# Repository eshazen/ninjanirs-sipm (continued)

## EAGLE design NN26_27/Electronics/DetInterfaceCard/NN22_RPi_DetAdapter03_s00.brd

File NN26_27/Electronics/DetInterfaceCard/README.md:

## Detector card V03

Two variants:

| Designator | NN24-26        | NN27  | Notes                             |
|------------|----------------|-------|-----------------------------------|
| R71        | DNP            | 0 Ohm | New component / designator        |
| LF1        | BLM18AG601SN1D | DNP   | Ferrite 600 Ohm @ 100 MHz, 500 mA |

Additional components could be DNP’d in NN27 if desired, such as U13 and C104.

**2026-08-24**

Trying to order.  Two problem parts:

C89 etc.  10uF X5R 0402

D1-D2  SBR1A20T5-7  1A fast response diode.  A problem.

Possible sub:  SBR1U40LP-7 in DFN package about the same size.
Make this change in `develop` (KiCAD conversion).  Layout done.

BOM is a problem... the KiCAD import doesnt include MPN.

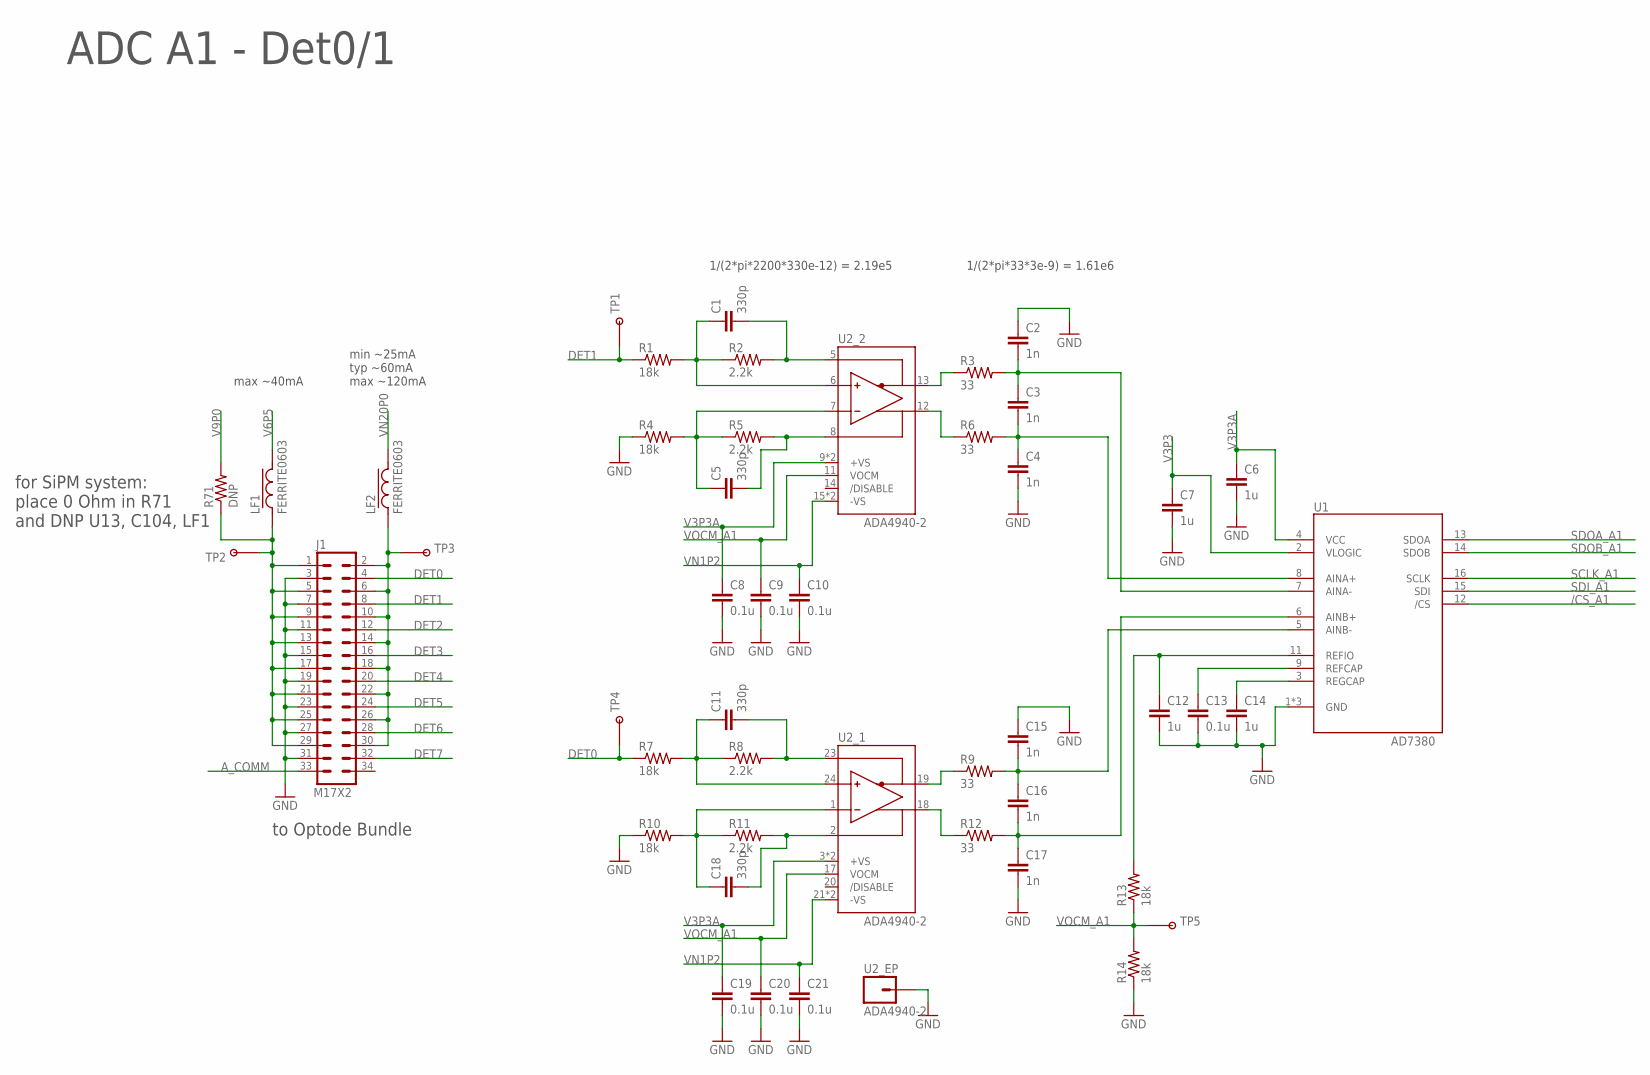
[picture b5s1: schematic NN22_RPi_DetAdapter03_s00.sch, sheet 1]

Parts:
C1, C5, C11, C18: 330p; 0402-CAP
C2, C3, C4, C15, C16, C17: 1n; 0402-CAP
C6, C7, C12, C14: 1u; 0402-CAP
C8, C9, C10, C13, C19, C20, C21: 0.1u; 0402-CAP
J1: M17X2; M17X2_0.050_SHF
LF1, LF2: FERRITE0603; 0603-FER
R1, R4, R7, R10, R13, R14: 18k; 0402-RES
R2, R5, R8, R11: 2.2k; 0402-RES
R3, R6, R9, R12: 33; 0402-RES
R71: DNP; 0402-RES
TP1, TP2, TP3, TP4, TP5: TESTPOINT_ROUND; TESTPAD_ROUND
U1: AD7380; LFCSP16
U2: ADA4940-2; LFCSP24

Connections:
/CS_A1: U1.12 (/CS); also elsewhere on the board
A_COMM: J1.33; also elsewhere on the board
DET0: J1.4, R7.1, TP4.P$1
DET1: J1.8, R1.1, TP1.P$1
DET2: J1.12; also elsewhere on the board
DET3: J1.16; also elsewhere on the board
DET4: J1.20; also elsewhere on the board
DET5: J1.24; also elsewhere on the board
DET6: J1.28; also elsewhere on the board
DET7: J1.32; also elsewhere on the board
GND: C2.1, C4.2, C6.2, C7.2, C8.2, C9.2, C10.2, C12.2, C13.2, C14.2, C15.1, C17.2, C19.2, C20.2, C21.2, J1.3, J1.7, J1.11, J1.15, J1.19, J1.23, J1.27, J1.31, R4.1, R10.1, R14.1, U1.1 (GND), U1.10 (GND), U1.EP (GND), U2.EP (1); also elsewhere on the board
unnamed: R3.1, U2.13 (-OUT)
unnamed: R6.1, U2.12 (+OUT)
unnamed: C2.2, C3.1, R3.2, U1.7 (AINA-)
unnamed: C3.2, C4.1, R6.2, U1.8 (AINA+)
unnamed: C11.2, R8.2, U2.23 (-FB)
unnamed: C12.1, R13.2, U1.11 (REFIO)
unnamed: C13.1, U1.9 (REFCAP)
unnamed: C14.1, U1.3 (REGCAP)
unnamed: C18.2, R11.2, U2.2 (+FB)
unnamed: R9.1, U2.19 (-OUT)
unnamed: R12.1, U2.18 (+OUT)
unnamed: C15.2, C16.1, R9.2, U1.5 (AINB-)
unnamed: C16.2, C17.1, R12.2, U1.6 (AINB+)
unnamed: C1.1, R1.2, R2.1, U2.6 (+IN)
unnamed: C1.2, R2.2, U2.5 (-FB)
unnamed: C5.2, R5.2, U2.8 (+FB)
unnamed: C5.1, R4.2, R5.1, U2.7 (-IN)
unnamed: C11.1, R7.2, R8.1, U2.24 (+IN)
unnamed: C18.1, R10.2, R11.1, U2.1 (-IN)
SCLK_A1: U1.16 (SCLK); also elsewhere on the board
SDI_A1: U1.15 (SDI); also elsewhere on the board
SDOA_A1: U1.13 (SDOA); also elsewhere on the board
SDOB_A1: U1.14 (SDOB); also elsewhere on the board
V3P3: C7.1, U1.2 (VLOGIC); also elsewhere on the board
V3P3A: C6.1, C8.1, C19.1, U1.4 (VCC), U2.3 (+VS), U2.4 (+VS), U2.9 (+VS), U2.10 (+VS); also elsewhere on the board
V6P5: LF1.2; also elsewhere on the board
V6P5CON: J1.1, J1.5, J1.9, J1.13, J1.17, J1.21, J1.25, J1.29, LF1.1, R71.1, TP2.P$1
V9P0: R71.2; also elsewhere on the board
VN1P2: C10.1, C21.1, U2.15 (-VS), U2.16 (-VS), U2.21 (-VS), U2.22 (-VS); also elsewhere on the board
VN20P0: LF2.2; also elsewhere on the board
VN20P0CON: J1.2, J1.6, J1.10, J1.14, J1.18, J1.22, J1.26, J1.30, LF2.1, TP3.P$1
VOCM_A1: C9.1, C20.1, R13.1, R14.2, TP5.P$1, U2.11 (VOCM), U2.17 (VOCM)

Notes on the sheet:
max ~40mA
min ~25mA typ ~60mA max ~120mA
to Optode Bundle
ADC A1 - Det0/1
1/(2*pi*33*3e-9) = 1.61e6
1/(2*pi*2200*330e-12) = 2.19e5
for SiPM system: place 0 Ohm in R71 and DNP U13, C104, LF1

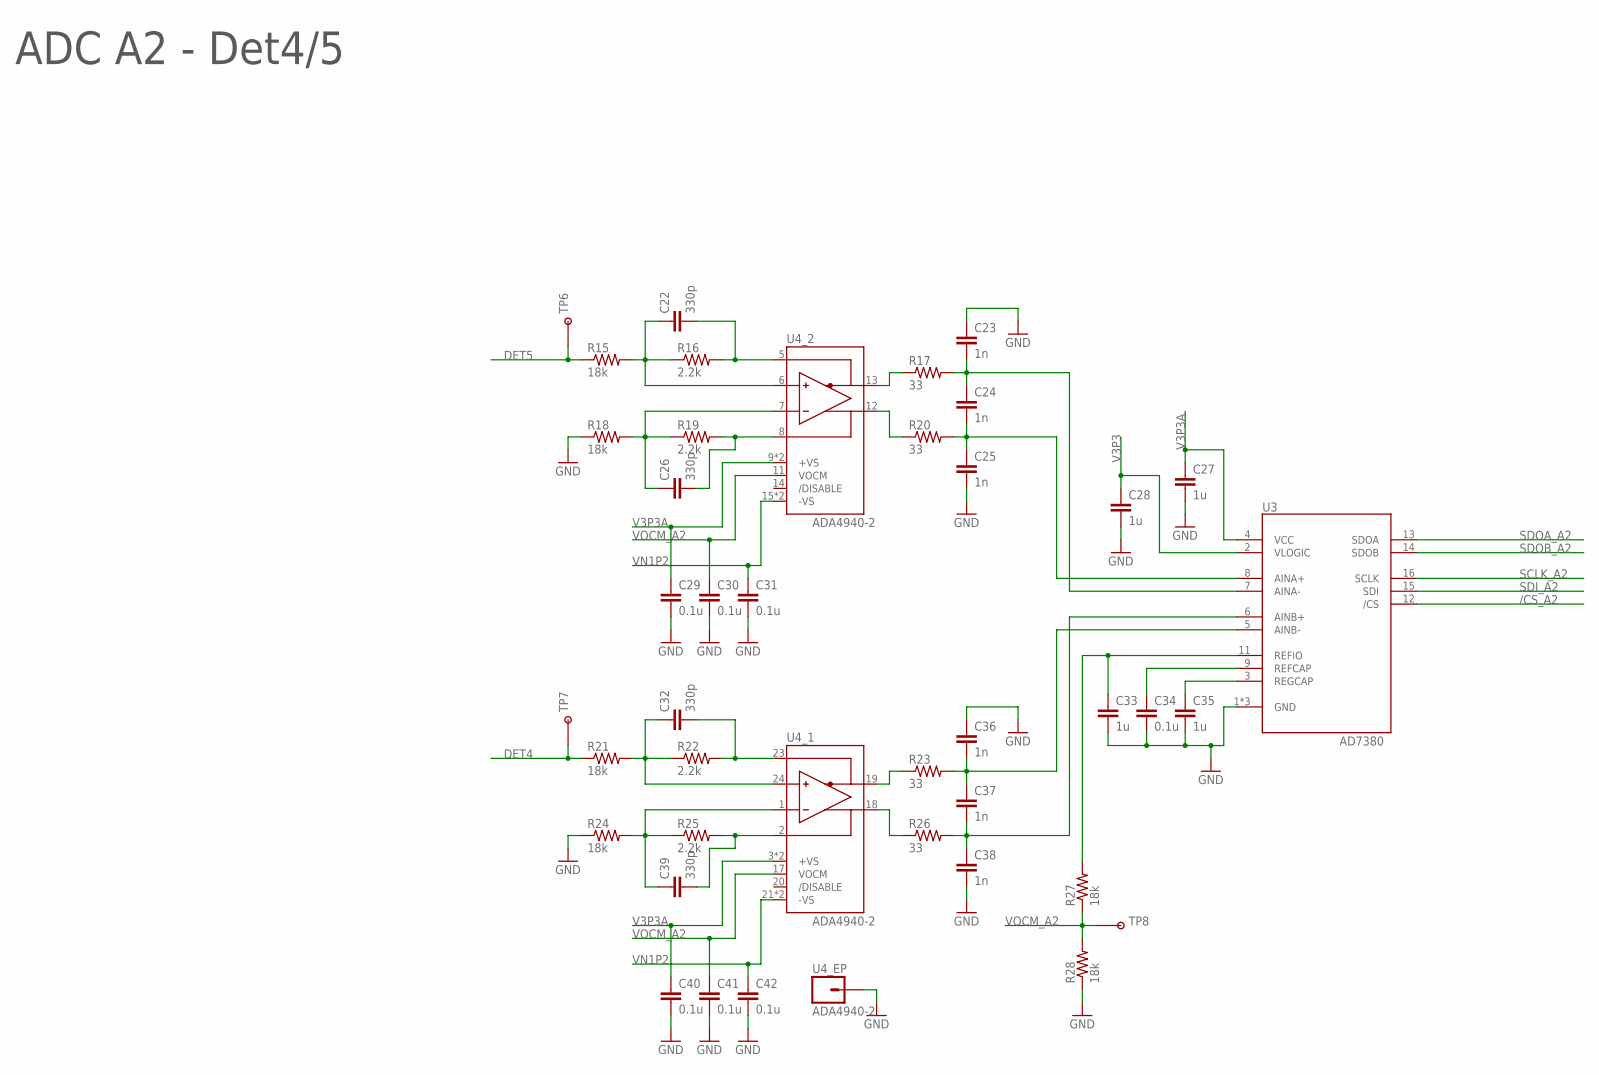
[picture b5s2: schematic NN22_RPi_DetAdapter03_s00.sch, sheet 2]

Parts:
C22, C26, C32, C39: 330p; 0402-CAP
C23, C24, C25, C36, C37, C38: 1n; 0402-CAP
C27, C28, C33, C35: 1u; 0402-CAP
C29, C30, C31, C34, C40, C41, C42: 0.1u; 0402-CAP
R15, R18, R21, R24, R27, R28: 18k; 0402-RES
R16, R19, R22, R25: 2.2k; 0402-RES
R17, R20, R23, R26: 33; 0402-RES
TP6, TP7, TP8: TESTPOINT_ROUND; TESTPAD_ROUND
U3: AD7380; LFCSP16
U4: ADA4940-2; LFCSP24

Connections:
/CS_A2: U3.12 (/CS); also elsewhere on the board
DET4: R21.1, TP7.P$1; also elsewhere on the board
DET5: R15.1, TP6.P$1; also elsewhere on the board
GND: C23.1, C25.2, C27.2, C28.2, C29.2, C30.2, C31.2, C33.2, C34.2, C35.2, C36.1, C38.2, C40.2, C41.2, C42.2, R18.1, R24.1, R28.1, U3.1 (GND), U3.10 (GND), U3.EP (GND), U4.EP (1); also elsewhere on the board
unnamed: R17.1, U4.13 (-OUT)
unnamed: R20.1, U4.12 (+OUT)
unnamed: C23.2, C24.1, R17.2, U3.7 (AINA-)
unnamed: C24.2, C25.1, R20.2, U3.8 (AINA+)
unnamed: C33.1, R27.2, U3.11 (REFIO)
unnamed: C34.1, U3.9 (REFCAP)
unnamed: C35.1, U3.3 (REGCAP)
unnamed: R23.1, U4.19 (-OUT)
unnamed: R26.1, U4.18 (+OUT)
unnamed: C36.2, C37.1, R23.2, U3.5 (AINB-)
unnamed: C37.2, C38.1, R26.2, U3.6 (AINB+)
unnamed: C22.1, R15.2, R16.1, U4.6 (+IN)
unnamed: C22.2, R16.2, U4.5 (-FB)
unnamed: C26.2, R19.2, U4.8 (+FB)
unnamed: C26.1, R18.2, R19.1, U4.7 (-IN)
unnamed: C32.1, R21.2, R22.1, U4.24 (+IN)
unnamed: C39.1, R24.2, R25.1, U4.1 (-IN)
unnamed: C32.2, R22.2, U4.23 (-FB)
unnamed: C39.2, R25.2, U4.2 (+FB)
SCLK_A2: U3.16 (SCLK); also elsewhere on the board
SDI_A2: U3.15 (SDI); also elsewhere on the board
SDOA_A2: U3.13 (SDOA); also elsewhere on the board
SDOB_A2: U3.14 (SDOB); also elsewhere on the board
V3P3: C28.1, U3.2 (VLOGIC); also elsewhere on the board
V3P3A: C27.1, C29.1, C40.1, U3.4 (VCC), U4.3 (+VS), U4.4 (+VS), U4.9 (+VS), U4.10 (+VS); also elsewhere on the board
VN1P2: C31.1, C42.1, U4.15 (-VS), U4.16 (-VS), U4.21 (-VS), U4.22 (-VS); also elsewhere on the board
VOCM_A2: C30.1, C41.1, R27.1, R28.2, TP8.P$1, U4.11 (VOCM), U4.17 (VOCM)

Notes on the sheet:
ADC A2 - Det4/5

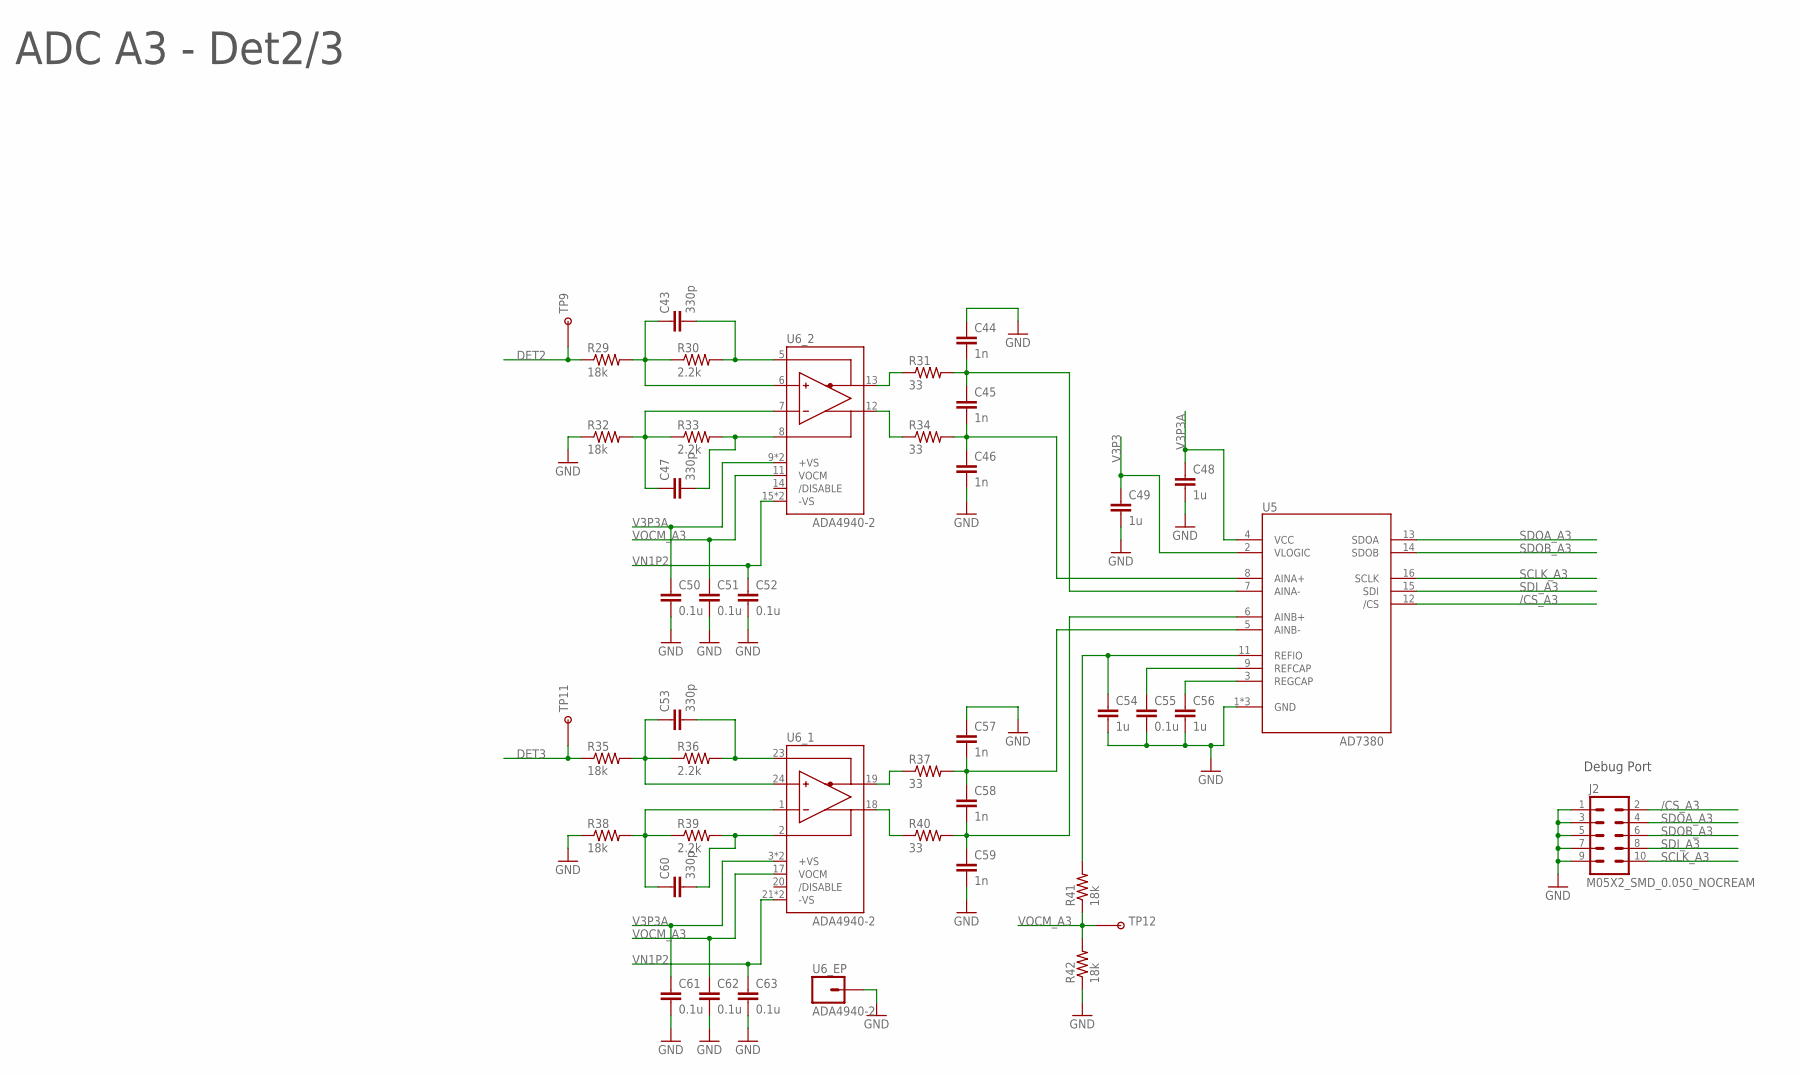
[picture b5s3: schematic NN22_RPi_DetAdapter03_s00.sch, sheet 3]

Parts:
C43, C47, C53, C60: 330p; 0402-CAP
C44, C45, C46, C57, C58, C59: 1n; 0402-CAP
C48, C49, C54, C56: 1u; 0402-CAP
C50, C51, C52, C55, C61, C62, C63: 0.1u; 0402-CAP
J2: M05X2_SMD_0.050_NOCREAM; M05X2_0.050_SMD_NO_CREAM
R29, R32, R35, R38, R41, R42: 18k; 0402-RES
R30, R33, R36, R39: 2.2k; 0402-RES
R31, R34, R37, R40: 33; 0402-RES
TP9, TP11, TP12: TESTPOINT_ROUND; TESTPAD_ROUND
U5: AD7380; LFCSP16
U6: ADA4940-2; LFCSP24

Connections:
/CS_A3: J2.2, U5.12 (/CS); also elsewhere on the board
DET2: R29.1, TP9.P$1; also elsewhere on the board
DET3: R35.1, TP11.P$1; also elsewhere on the board
GND: C44.1, C46.2, C48.2, C49.2, C50.2, C51.2, C52.2, C54.2, C55.2, C56.2, C57.1, C59.2, C61.2, C62.2, C63.2, J2.1, J2.3, J2.5, J2.7, J2.9, R32.1, R38.1, R42.1, U5.1 (GND), U5.10 (GND), U5.EP (GND), U6.EP (1); also elsewhere on the board
unnamed: R31.1, U6.13 (-OUT)
unnamed: R34.1, U6.12 (+OUT)
unnamed: C44.2, C45.1, R31.2, U5.7 (AINA-)
unnamed: C45.2, C46.1, R34.2, U5.8 (AINA+)
unnamed: C54.1, R41.2, U5.11 (REFIO)
unnamed: C55.1, U5.9 (REFCAP)
unnamed: C56.1, U5.3 (REGCAP)
unnamed: R37.1, U6.19 (-OUT)
unnamed: R40.1, U6.18 (+OUT)
unnamed: C57.2, C58.1, R37.2, U5.5 (AINB-)
unnamed: C58.2, C59.1, R40.2, U5.6 (AINB+)
unnamed: C43.1, R29.2, R30.1, U6.6 (+IN)
unnamed: C43.2, R30.2, U6.5 (-FB)
unnamed: C47.2, R33.2, U6.8 (+FB)
unnamed: C47.1, R32.2, R33.1, U6.7 (-IN)
unnamed: C53.1, R35.2, R36.1, U6.24 (+IN)
unnamed: C60.1, R38.2, R39.1, U6.1 (-IN)
unnamed: C53.2, R36.2, U6.23 (-FB)
unnamed: C60.2, R39.2, U6.2 (+FB)
SCLK_A3: J2.10, U5.16 (SCLK); also elsewhere on the board
SDI_A3: J2.8, U5.15 (SDI); also elsewhere on the board
SDOA_A3: J2.4, U5.13 (SDOA); also elsewhere on the board
SDOB_A3: J2.6, U5.14 (SDOB); also elsewhere on the board
V3P3: C49.1, U5.2 (VLOGIC); also elsewhere on the board
V3P3A: C48.1, C50.1, C61.1, U5.4 (VCC), U6.3 (+VS), U6.4 (+VS), U6.9 (+VS), U6.10 (+VS); also elsewhere on the board
VN1P2: C52.1, C63.1, U6.15 (-VS), U6.16 (-VS), U6.21 (-VS), U6.22 (-VS); also elsewhere on the board
VOCM_A3: C51.1, C62.1, R41.1, R42.2, TP12.P$1, U6.11 (VOCM), U6.17 (VOCM)

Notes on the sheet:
Debug Port
ADC A3 - Det2/3

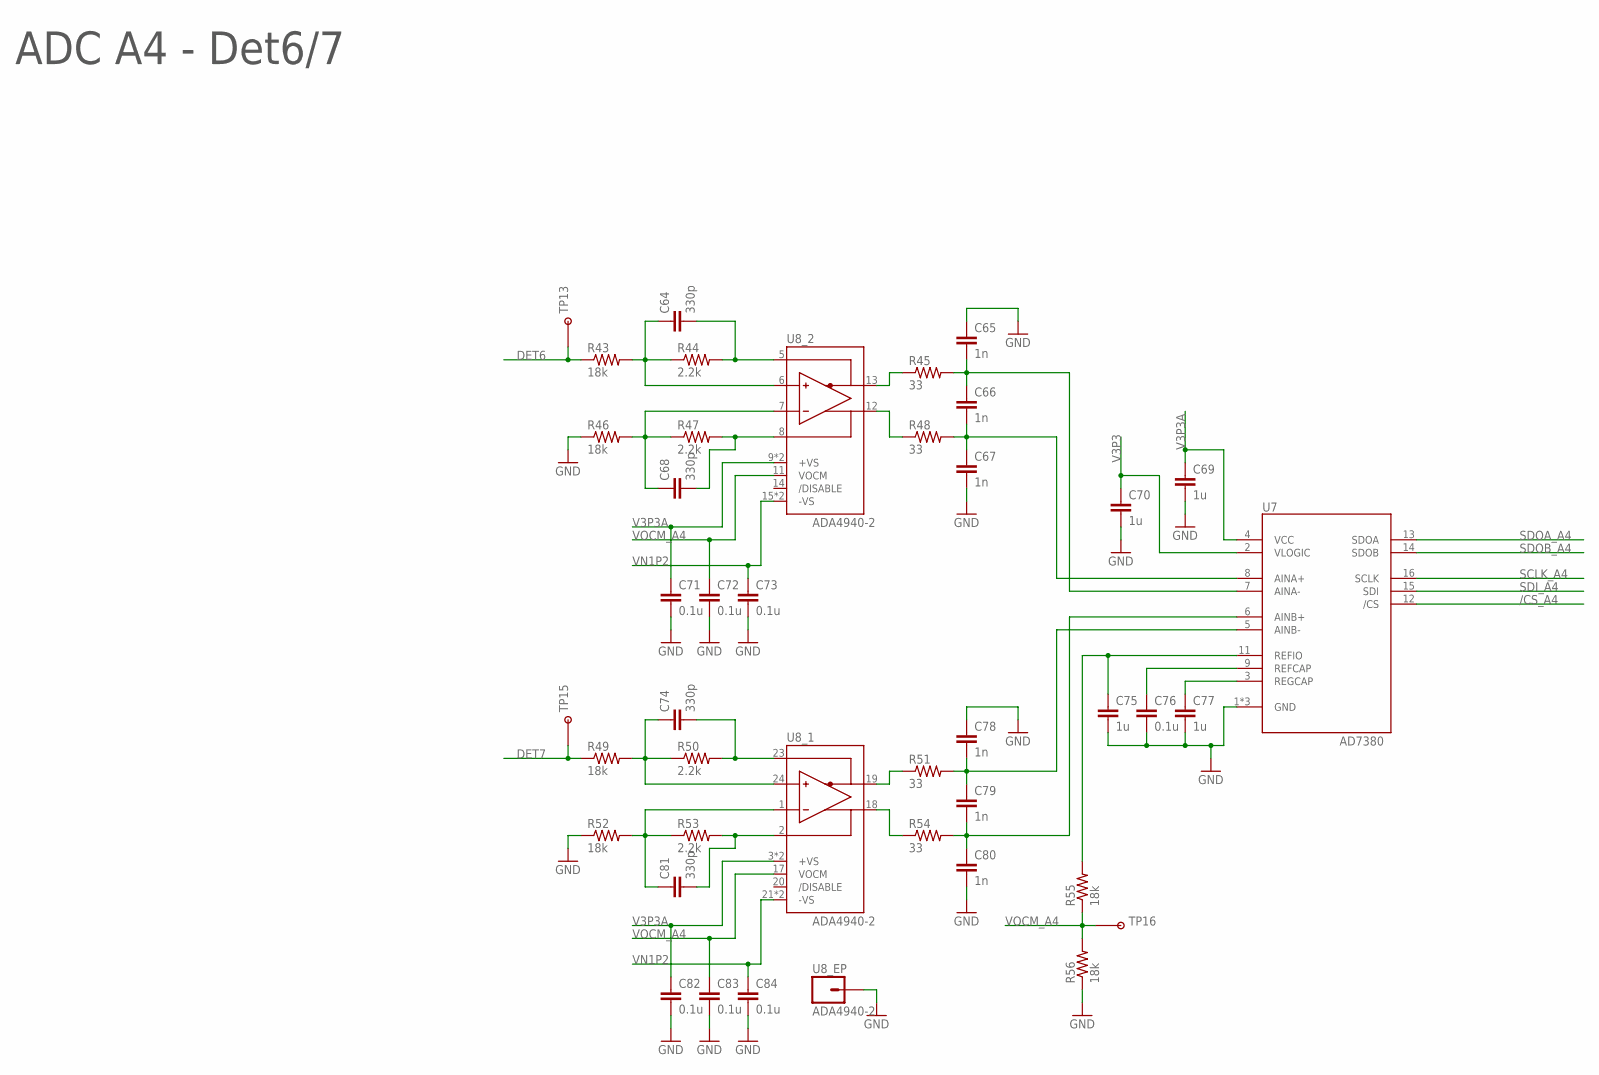
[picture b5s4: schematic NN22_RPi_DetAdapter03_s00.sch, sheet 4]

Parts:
C64, C68, C74, C81: 330p; 0402-CAP
C65, C66, C67, C78, C79, C80: 1n; 0402-CAP
C69, C70, C75, C77: 1u; 0402-CAP
C71, C72, C73, C76, C82, C83, C84: 0.1u; 0402-CAP
R43, R46, R49, R52, R55, R56: 18k; 0402-RES
R44, R47, R50, R53: 2.2k; 0402-RES
R45, R48, R51, R54: 33; 0402-RES
TP13, TP15, TP16: TESTPOINT_ROUND; TESTPAD_ROUND
U7: AD7380; LFCSP16
U8: ADA4940-2; LFCSP24

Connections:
/CS_A4: U7.12 (/CS); also elsewhere on the board
DET6: R43.1, TP13.P$1; also elsewhere on the board
DET7: R49.1, TP15.P$1; also elsewhere on the board
GND: C65.1, C67.2, C69.2, C70.2, C71.2, C72.2, C73.2, C75.2, C76.2, C77.2, C78.1, C80.2, C82.2, C83.2, C84.2, R46.1, R52.1, R56.1, U7.1 (GND), U7.10 (GND), U7.EP (GND), U8.EP (1); also elsewhere on the board
unnamed: R45.1, U8.13 (-OUT)
unnamed: R48.1, U8.12 (+OUT)
unnamed: C65.2, C66.1, R45.2, U7.7 (AINA-)
unnamed: C66.2, C67.1, R48.2, U7.8 (AINA+)
unnamed: C75.1, R55.2, U7.11 (REFIO)
unnamed: C76.1, U7.9 (REFCAP)
unnamed: C77.1, U7.3 (REGCAP)
unnamed: R51.1, U8.19 (-OUT)
unnamed: R54.1, U8.18 (+OUT)
unnamed: C78.2, C79.1, R51.2, U7.5 (AINB-)
unnamed: C79.2, C80.1, R54.2, U7.6 (AINB+)
unnamed: C64.1, R43.2, R44.1, U8.6 (+IN)
unnamed: C64.2, R44.2, U8.5 (-FB)
unnamed: C68.2, R47.2, U8.8 (+FB)
unnamed: C68.1, R46.2, R47.1, U8.7 (-IN)
unnamed: C74.1, R49.2, R50.1, U8.24 (+IN)
unnamed: C81.1, R52.2, R53.1, U8.1 (-IN)
unnamed: C74.2, R50.2, U8.23 (-FB)
unnamed: C81.2, R53.2, U8.2 (+FB)
SCLK_A4: U7.16 (SCLK); also elsewhere on the board
SDI_A4: U7.15 (SDI); also elsewhere on the board
SDOA_A4: U7.13 (SDOA); also elsewhere on the board
SDOB_A4: U7.14 (SDOB); also elsewhere on the board
V3P3: C70.1, U7.2 (VLOGIC); also elsewhere on the board
V3P3A: C69.1, C71.1, C82.1, U7.4 (VCC), U8.3 (+VS), U8.4 (+VS), U8.9 (+VS), U8.10 (+VS); also elsewhere on the board
VN1P2: C73.1, C84.1, U8.15 (-VS), U8.16 (-VS), U8.21 (-VS), U8.22 (-VS); also elsewhere on the board
VOCM_A4: C72.1, C83.1, R55.1, R56.2, TP16.P$1, U8.11 (VOCM), U8.17 (VOCM)

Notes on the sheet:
ADC A4 - Det6/7

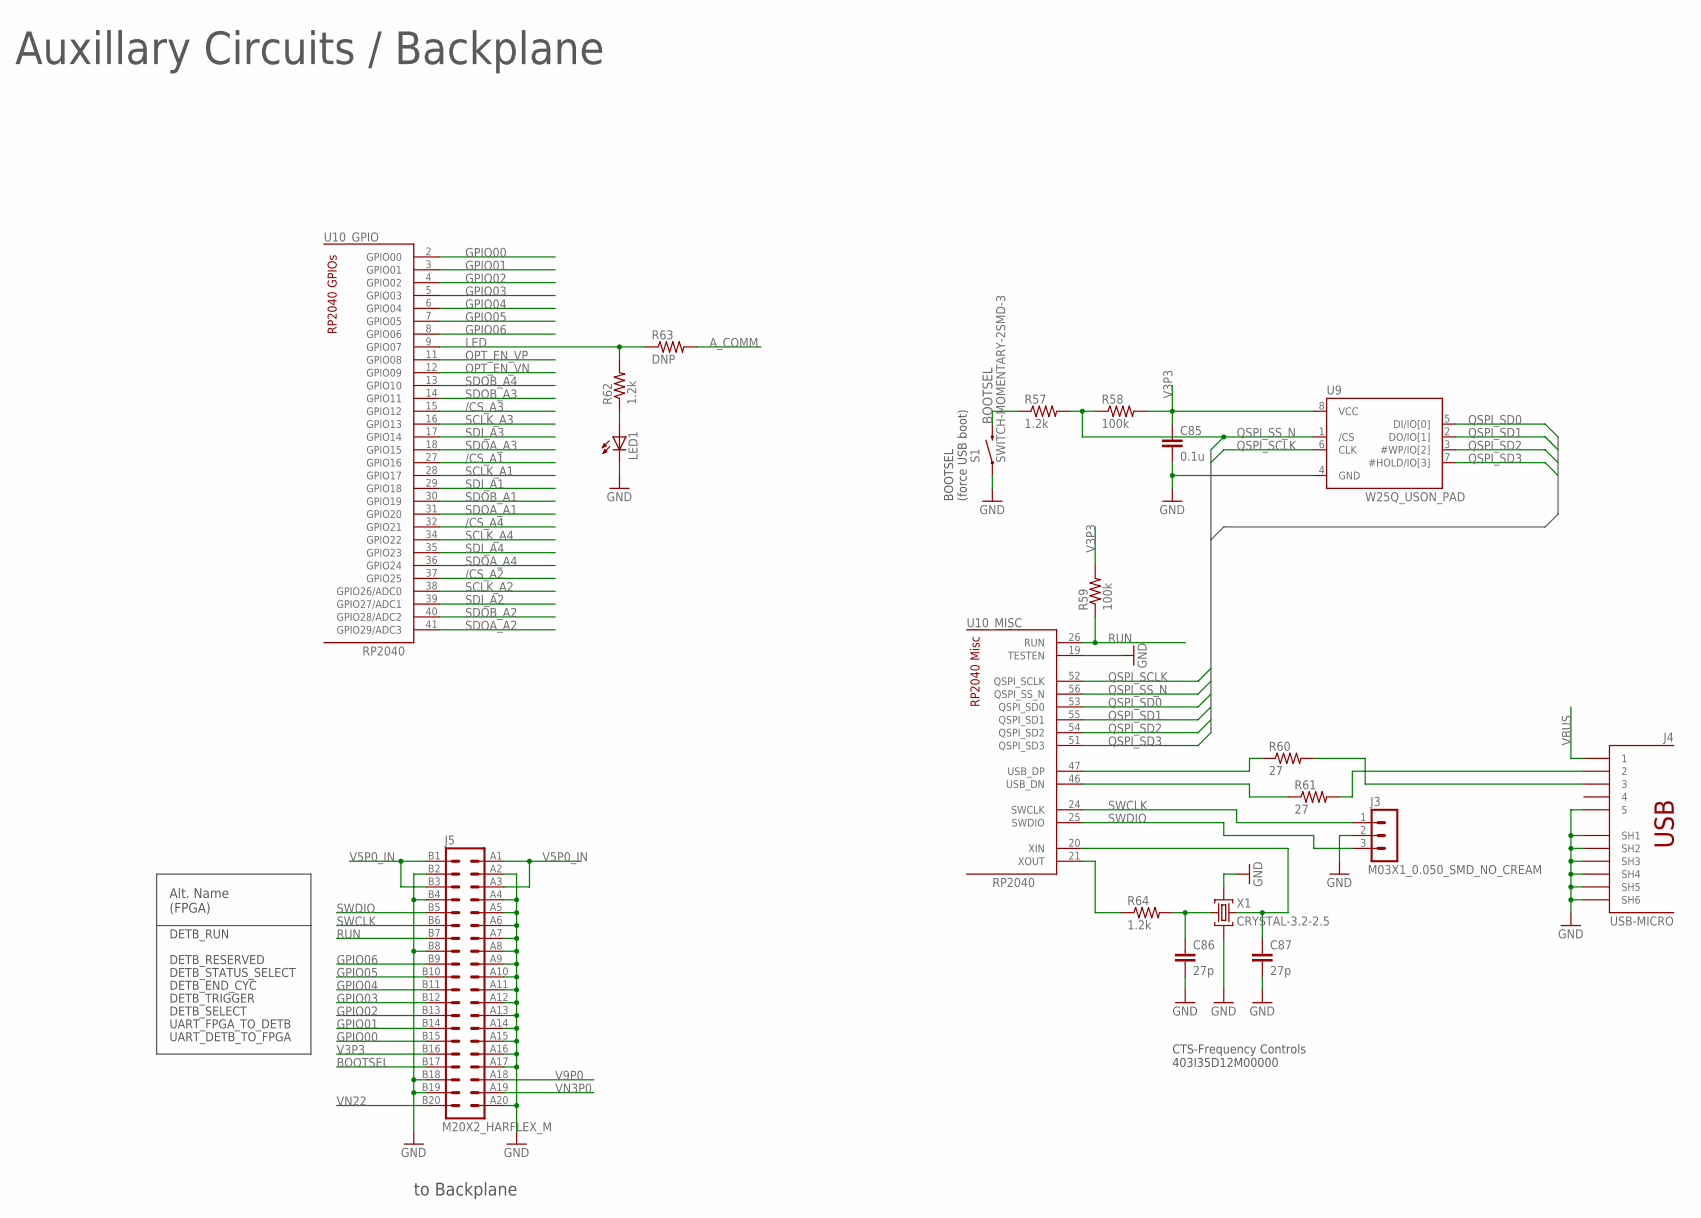
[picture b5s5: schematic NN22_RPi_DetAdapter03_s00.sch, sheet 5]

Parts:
C85: 0.1u; 0402-CAP
C86, C87: 27p; 0402-CAP
J3: M03X1_0.050_SMD_NO_CREAM
J4: USB-MICRO
J5: M20X2_HARFLEX_M
LED1: LED0603; LED-0603
R57, R62, R64: 1.2k; 0402-RES
R58, R59: 100k; 0402-RES
R60, R61: 27; 0402-RES
R63: DNP; 0402-RES
S1: SWITCH-MOMENTARY-2SMD-3; TACTILE_SWITCH_SMD-3
U9: W25Q_USON_PAD; USON8L-2X3MM_APM
U10: RP2040; QFN-56_EP
X1: CRYSTAL-3.2-2.5

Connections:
/CS_A1: U10.27 (GPIO16); also elsewhere on the board
/CS_A2: U10.37 (GPIO25); also elsewhere on the board
/CS_A3: U10.15 (GPIO12); also elsewhere on the board
/CS_A4: U10.32 (GPIO21); also elsewhere on the board
A_COMM: R63.2; also elsewhere on the board
BOOTSEL: J5.B17 (33), R57.1, S1.4 (2)
GND: C85.2, C86.2, C87.2, J3.2, J4.5, J4.SH1, J4.SH2, J4.SH3, J4.SH4, J4.SH5, J4.SH6, J5.A2 (4), J5.A4 (8), J5.A5 (10), J5.A6 (12), J5.A7 (14), J5.A8 (16), J5.A9 (18), J5.A10 (20), J5.A11 (22), J5.A12 (24), J5.A13 (26), J5.A14 (28), J5.A15 (30), J5.A16 (32), J5.A17 (34), J5.A20 (40), J5.B2 (3), J5.B4 (7), J5.B8 (15), J5.B18 (35), J5.B19 (37), LED1.C, S1.1, U9.4 (GND), U10.19 (TESTEN), X1.2 (GND), X1.4 (GND); also elsewhere on the board
GPIO00: J5.B15 (29), U10.2 (GPIO00)
GPIO01: J5.B14 (27), U10.3 (GPIO01)
GPIO02: J5.B13 (25), U10.4 (GPIO02)
GPIO03: J5.B12 (23), U10.5 (GPIO03)
GPIO04: J5.B11 (21), U10.6 (GPIO04)
GPIO05: J5.B10 (19), U10.7 (GPIO05)
GPIO06: J5.B9 (17), U10.8 (GPIO06)
LED: R62.2, R63.1, U10.9 (GPIO07)
unnamed: C87.1, U10.20 (XIN), X1.3 (C2)
unnamed: C86.1, R64.2, X1.1 (C1)
unnamed: R64.1, U10.21 (XOUT)
unnamed: R60.1, U10.47 (USB_DP)
unnamed: R61.1, U10.46 (USB_DN)
unnamed: J4.2, R61.2
unnamed: J4.3, R60.2
unnamed: LED1.A, R62.1
OPT_EN_VN: U10.12 (GPIO09); also elsewhere on the board
OPT_EN_VP: U10.11 (GPIO08); also elsewhere on the board
QSPI_SCLK: U9.6 (CLK), U10.52 (QSPI_SCLK)
QSPI_SD0: U9.5 (DI/IO[0]), U10.53 (QSPI_SD0)
QSPI_SD1: U9.2 (DO/IO[1]), U10.55 (QSPI_SD1)
QSPI_SD2: U9.3 (#WP/IO[2]), U10.54 (QSPI_SD2)
QSPI_SD3: U9.7 (#HOLD/IO[3]), U10.51 (QSPI_SD3)
QSPI_SS_N: R57.2, R58.1, U9.1 (/CS), U10.56 (QSPI_SS_N)
RUN: J5.B7 (13), R59.1, U10.26 (RUN)
SCLK_A1: U10.28 (GPIO17); also elsewhere on the board
SCLK_A2: U10.38 (GPIO26/ADC0); also elsewhere on the board
SCLK_A3: U10.16 (GPIO13); also elsewhere on the board
SCLK_A4: U10.34 (GPIO22); also elsewhere on the board
SDI_A1: U10.29 (GPIO18); also elsewhere on the board
SDI_A2: U10.39 (GPIO27/ADC1); also elsewhere on the board
SDI_A3: U10.17 (GPIO14); also elsewhere on the board
SDI_A4: U10.35 (GPIO23); also elsewhere on the board
SDOA_A1: U10.31 (GPIO20); also elsewhere on the board
SDOA_A2: U10.41 (GPIO29/ADC3); also elsewhere on the board
SDOA_A3: U10.18 (GPIO15); also elsewhere on the board
SDOA_A4: U10.36 (GPIO24); also elsewhere on the board
SDOB_A1: U10.30 (GPIO19); also elsewhere on the board
SDOB_A2: U10.40 (GPIO28/ADC2); also elsewhere on the board
SDOB_A3: U10.14 (GPIO11); also elsewhere on the board
SDOB_A4: U10.13 (GPIO10); also elsewhere on the board
SWCLK: J3.1, J5.B6 (11), U10.24 (SWCLK)
SWDIO: J3.3, J5.B5 (9), U10.25 (SWDIO)
V3P3: C85.1, J5.B16 (31), R58.2, R59.2, U9.8 (VCC); also elsewhere on the board
V5P0_IN: J5.A1 (2), J5.A3 (6), J5.B1 (1), J5.B3 (5); also elsewhere on the board
V9P0: J5.A18 (36); also elsewhere on the board
VBUS: J4.1; also elsewhere on the board
VN3P0: J5.A19 (38); also elsewhere on the board
VN22: J5.B20 (39); also elsewhere on the board

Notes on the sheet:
BOOTSEL (force USB boot)
Auxillary Circuits / Backplane
to Backplane
CTS-Frequency Controls 403I35D12M00000
UART_DETB_TO_FPGA
UART_FPGA_TO_DETB
DETB_SELECT
DETB_TRIGGER
DETB_END_CYC
DETB_STATUS_SELECT
DETB_RESERVED
DETB_RUN
Alt. Name (FPGA)

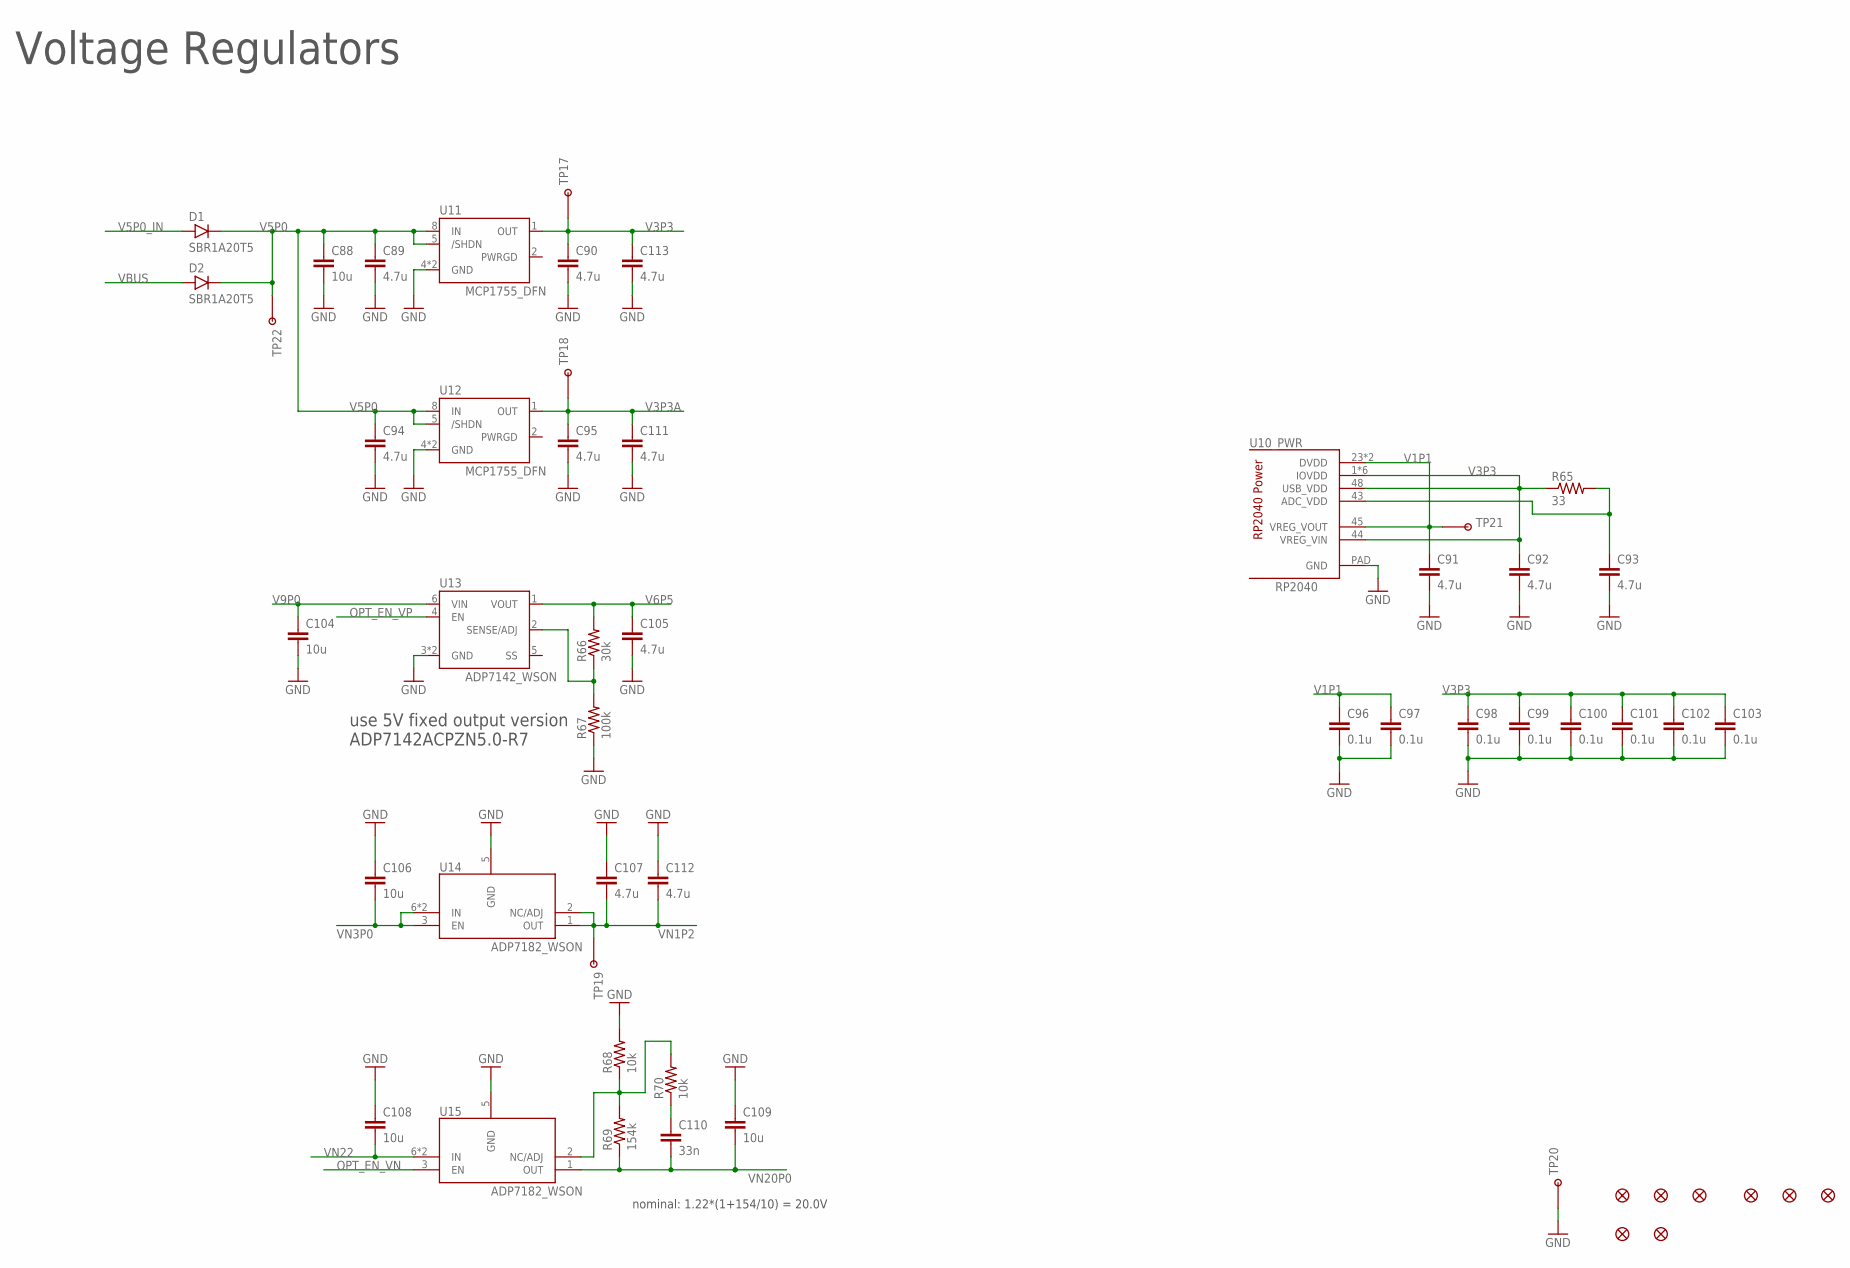
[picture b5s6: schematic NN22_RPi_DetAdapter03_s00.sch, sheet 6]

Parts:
C88, C104, C106, C108, C109: 10u; 0603-CAP
C89, C90, C91, C92, C93, C94, C95, C105, C107, C111, C112, C113: 4.7u; 0402-CAP
C96, C97, C98, C99, C100, C101, C102, C103: 0.1u; 0402-CAP
C110: 33n; 0402-CAP
D1, D2: SBR1A20T5; SOD523
FID1, FID2, FID3, FID4, FID5, FID6, FID7, FID8: FIDUCIALUFIDUCIAL; MICRO-FIDUCIAL
R65: 33; 0402-RES
R66: 30k; 0402-RES
R67: 100k; 0402-RES
R68, R70: 10k; 0402-RES
R69: 154k; 0402-RES
TP17, TP18, TP19, TP22: TESTPOINT_ROUND; TESTPAD_ROUND
TP20: TESTPOINT1X01; 1X01
TP21: TESTPOINTPADSMALL; TESTPAD_SMALL
U10: RP2040; QFN-56_EP
U11, U12: MCP1755_DFN; DFN8_2X3MM
U13: ADP7142_WSON; WSON6
U14, U15: ADP7182_WSON; WSON6

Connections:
GND: C88.2, C89.2, C90.2, C91.2, C92.2, C93.2, C94.2, C95.2, C96.2, C97.2, C98.2, C99.2, C100.2, C101.2, C102.2, C103.2, C104.2, C105.2, C106.1, C107.1, C108.1, C109.1, C111.2, C112.1, C113.2, R67.1, R68.2, TP20.1, U10.PAD (GND), U11.4 (GND), U11.P (GND), U12.4 (GND), U12.P (GND), U13.3 (GND), U13.PAD (GND), U14.5 (GND), U15.5 (GND); also elsewhere on the board
unnamed: R68.1, R69.2, R70.2, U15.2 (NC/ADJ)
unnamed: R66.1, R67.2, U13.2 (SENSE/ADJ)
unnamed: C93.1, R65.2, U10.43 (ADC_VDD)
unnamed: C110.1, R70.1
OPT_EN_VN: U15.3 (EN); also elsewhere on the board
OPT_EN_VP: U13.4 (EN); also elsewhere on the board
V1P1: C91.1, C96.1, C97.1, TP21.P$1, U10.23 (DVDD), U10.45 (VREG_VOUT), U10.50 (DVDD)
V3P3: C90.1, C92.1, C98.1, C99.1, C100.1, C101.1, C102.1, C103.1, C113.1, R65.1, TP17.P$1, U10.1 (IOVDD), U10.10 (IOVDD), U10.22 (IOVDD), U10.33 (IOVDD), U10.42 (IOVDD), U10.44 (VREG_VIN), U10.48 (USB_VDD), U10.49 (IOVDD), U11.1 (OUT); also elsewhere on the board
V3P3A: C95.1, C111.1, TP18.P$1, U12.1 (OUT); also elsewhere on the board
V5P0: C88.1, C89.1, C94.1, D1.C, D2.C, TP22.P$1, U11.5 (/SHDN), U11.8 (IN), U12.5 (/SHDN), U12.8 (IN)
V5P0_IN: D1.A; also elsewhere on the board
V6P5: C105.1, R66.2, U13.1 (VOUT); also elsewhere on the board
V9P0: C104.1, U13.6 (VIN); also elsewhere on the board
VBUS: D2.A; also elsewhere on the board
VN1P2: C107.2, C112.2, TP19.P$1, U14.1 (OUT), U14.2 (NC/ADJ); also elsewhere on the board
VN3P0: C106.2, U14.3 (EN), U14.6 (IN), U14.PAD (IN); also elsewhere on the board
VN20P0: C109.2, C110.2, R69.1, U15.1 (OUT); also elsewhere on the board
VN22: C108.2, U15.6 (IN), U15.PAD (IN); also elsewhere on the board

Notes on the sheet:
use 5V fixed output version ADP7142ACPZN5.0-R7
Voltage Regulators
nominal: 1.22*(1+154/10) = 20.0V
